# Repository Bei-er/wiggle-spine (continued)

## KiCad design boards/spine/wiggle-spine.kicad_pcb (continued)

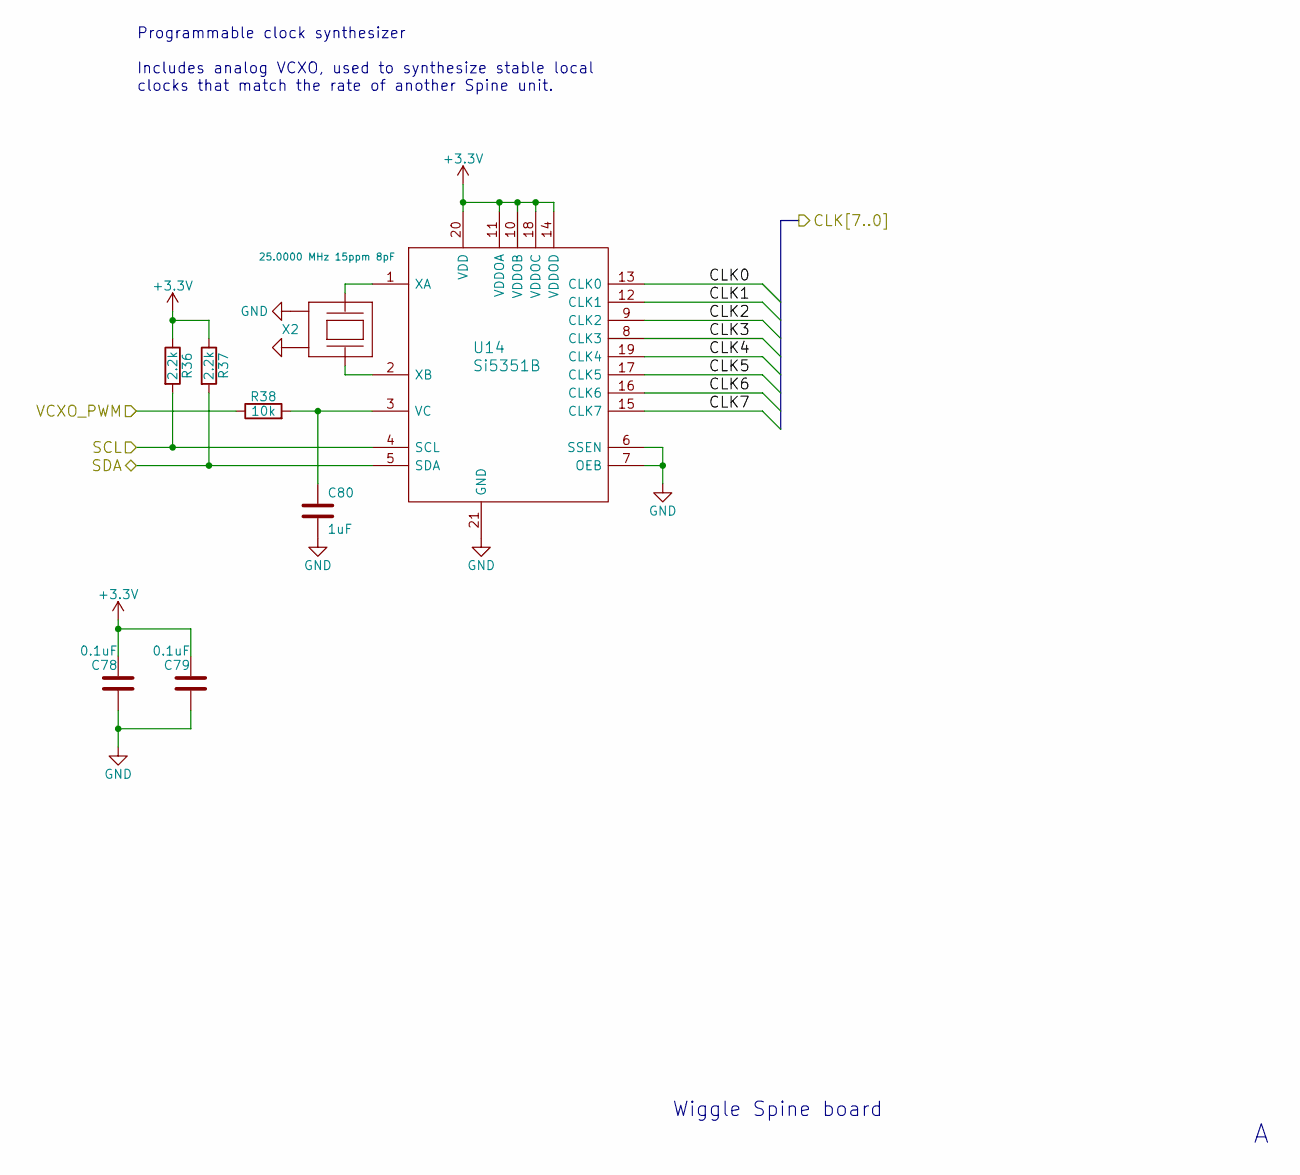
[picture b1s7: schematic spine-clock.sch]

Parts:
C78, C79: 0.1uF; C_0805
C80: 1uF; C_0805
R36, R37: 2.2k; R_0805
R38: 10k; R_0805
U14: Si5351B; QFN-20-1EP_4x4mm_Pitch0.5mm
X2: 25.0000 MHz 15ppm 8pF; crystal_FA238-TSX3225

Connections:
/Clock Source/CLK0: U14.13 (CLK0); also elsewhere on the board
/Clock Source/CLK1: U14.12 (CLK1); also elsewhere on the board
/Clock Source/CLK2: U14.9 (CLK2); also elsewhere on the board
/Clock Source/CLK3: U14.8 (CLK3); also elsewhere on the board
/Clock Source/CLK4: U14.19 (CLK4); also elsewhere on the board
/Clock Source/CLK5: U14.17 (CLK5); also elsewhere on the board
/Clock Source/CLK6: U14.16 (CLK6); also elsewhere on the board
/Clock Source/CLK7: U14.15 (CLK7); also elsewhere on the board
/Clock Source/VCXO_PWM: R38.1; also elsewhere on the board
/FPGA/CLK_SCL: R36.2, U14.4 (SCL); also elsewhere on the board
/FPGA/CLK_SDA: R37.2, U14.5 (SDA); also elsewhere on the board
GND: C78.1, C79.1, C80.2, U14.6 (SSEN), U14.7 (OEB), U14.21 (GND), X2.2, X2.4; also elsewhere on the board
unnamed: C80.1, R38.2, U14.3 (VC)
unnamed: U14.1 (XA), X2.1
unnamed: U14.2 (XB), X2.3

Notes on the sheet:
Programmable clock synthesizer Includes analog VCXO, used to synthesize stable local clocks that match the rate of another Spine unit.
Wiggle Spine board

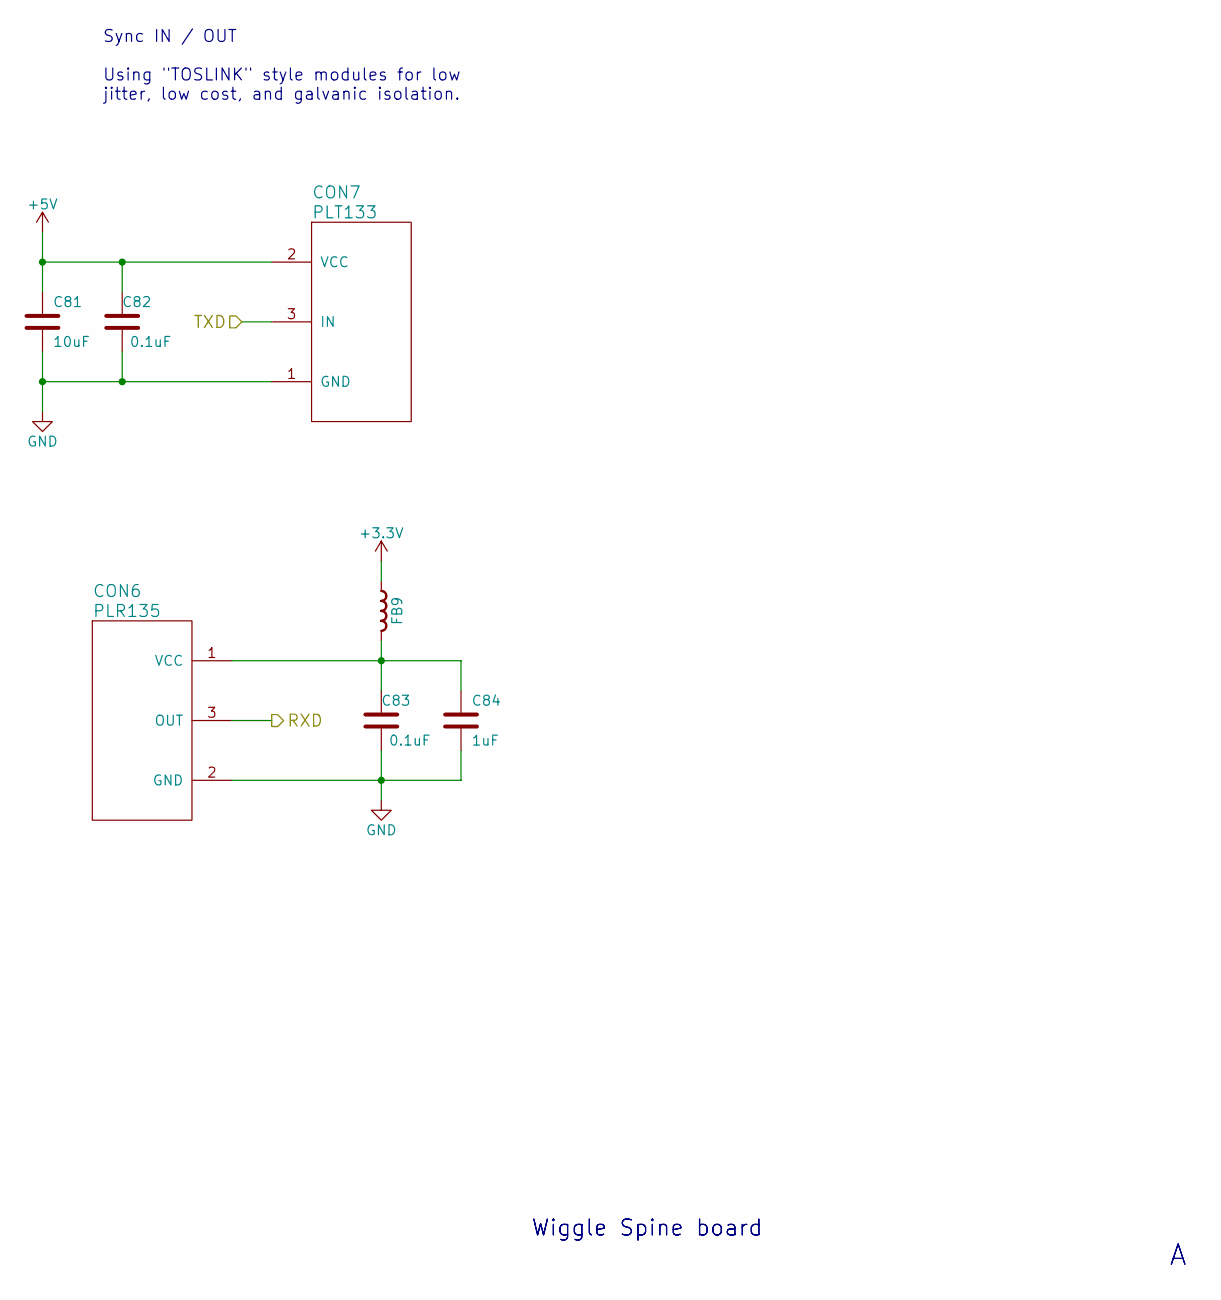
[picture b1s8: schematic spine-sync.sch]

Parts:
C81: 10uF; C_1206
C82, C83: 0.1uF; C_0805
C84: 1uF; C_0805
CON6: PLR135; Everlight-PLR135-T8
CON7: PLT133; Everlight-PLT133-T6A
FB9: Ferrite bead; R_0805

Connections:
+5V: C81.1, C82.2, CON7.2 (VCC); also elsewhere on the board
/FPGA/SYNC_TXD: CON7.3 (IN); also elsewhere on the board
/Sync In/Out/RXD: CON6.3 (OUT); also elsewhere on the board
GND: C81.2, C82.1, C83.1, C84.2, CON6.2 (GND), CON7.1 (GND); also elsewhere on the board
unnamed: C83.2, C84.1, CON6.1 (VCC), FB9.2

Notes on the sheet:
Sync IN / OUT Using "TOSLINK" style modules for low jitter, low cost, and galvanic isolation.
Wiggle Spine board

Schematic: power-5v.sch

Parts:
C43, C44, C50, C51: 22uF; c_elec_6.3x7.7
C45, C46, C52: 10uF; C_1206
C47: 1uF; C_0805
C48: 0.1uF; C_0805
C49: 100pF; C_0805
D6: BAT54 2x common cathode; SOT-23
L1: 22uH; Neosid_Inductor_SM-NE127
R23, R27: 100k; R_0805
R24: 150; R_0805
R25: 27k 1%; R_0805
R26: 5.1k 1%; R_0805
U7: RT8299A; SOIC-8-1EP_3.9x4.9mm_Pitch1.27mm

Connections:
+24V: C43.1, C44.1, C45.1, C46.1, R23.1, U7.2 (VIN); also elsewhere on the board
/Power/5-24V to 5V Converter/CONVERTED_5V_OKAY: R27.1, U7.7 (PGOOD); also elsewhere on the board
/Power/USB Power Output/5V_IN: C50.1, C51.1, C52.1, D6.1 (A), D6.2 (A), L1.2, R25.2, R27.2; also elsewhere on the board
GND: C43.2, C44.2, C45.2, C46.2, C47.2, C49.1, C50.2, C51.2, C52.2, R26.1, U7.4 (GND), U7.9 (GND); also elsewhere on the board
unnamed: C47.1, U7.8 (VCC)
unnamed: C48.1, L1.1, R24.2, U7.3 (SW)
unnamed: C48.2, D6.3 (K), U7.1 (BOOT)
unnamed: C49.2, R24.1
unnamed: R23.2, U7.6 (EN)
unnamed: R25.1, R26.2, U7.5 (FB)

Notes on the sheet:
Open drain output
Bootstrap assistance for Vin < 5.5
Wiggle Spine board
High efficiency DC-DC converter, 5V at 3A from 5-24V DC. This 5V rail is shared by the USB output (up to 2A), the modules (100mA each), and all FPGA and USB controller power rails.

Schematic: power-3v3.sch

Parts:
C53, C59, C60: 22uF; c_elec_6.3x7.7
C54, C55, C61: 10uF; C_1206
C56: 1uF; C_0805
C57: 0.1uF; C_0805
C58: 100pF; C_0805
D7: BAT54 2x common cathode; SOT-23
L2: 22uH; Neosid_Inductor_SM-NE127
R28: 150; R_0805
R29: 16k 1%; R_0805
R30: 5.1k 1%; R_0805
U8: RT8299A; SOIC-8-1EP_3.9x4.9mm_Pitch1.27mm

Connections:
+5V: C53.1, C54.1, C55.1, D7.1 (A), D7.2 (A), U8.2 (VIN), U8.6 (EN); also elsewhere on the board
GND: C53.2, C54.2, C55.2, C56.2, C58.1, C59.2, C60.2, C61.2, R30.1, U8.4 (GND), U8.9 (GND); also elsewhere on the board
unnamed: C56.1, U8.8 (VCC)
unnamed: C57.1, L2.1, R28.2, U8.3 (SW)
unnamed: C57.2, D7.3 (K), U8.1 (BOOT)
unnamed: C58.2, R28.1
unnamed: R29.1, R30.2, U8.5 (FB)

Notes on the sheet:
Bootstrap assistance diode; see RT8299A data sheet
Wiggle Spine board
High efficiency DC-DC converter, 3.3V at 3A

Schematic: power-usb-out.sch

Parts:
C62: 1uF; C_0805
C63, C64: 0.1uF; C_0805
CON3: USB-A; USB_A_Vertical
F2: 2A PTC; R_1812
FB5, FB6: Ferrite bead; R_0805
R31, R32: 100k; R_0805
U9: SiP32408; TDFN4

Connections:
/FPGA/VBUS_DOWNSTREAM_EN: R31.1, U9.3 (EN); also elsewhere on the board
/Power/USB Power Output/5V_IN: C62.1, R31.2, U9.1 (IN); also elsewhere on the board
Earth: CON3.5 (shield); also elsewhere on the board
GND: C62.2, C63.1, C64.1, FB6.1, R32.2, U9.2 (GND), U9.5 (GND); also elsewhere on the board
unnamed: C63.2, F2.1, R32.1, U9.4 (OUT)
unnamed: C64.2, F2.2, FB5.1
unnamed: CON3.1 (VCC), FB5.2
unnamed: CON3.2 (D-), CON3.3 (D+)
unnamed: CON3.4 (GND), FB6.2

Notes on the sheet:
Not the main +5V rail; this is intended to draw power from the DC-DC converter only, not the USB-B input.
USB power output, 5V 2A. Intended to power a small computer, like the Raspberry Pi 2. Optional hardware watchdog timer, implemented in the FPGA.
Wiggle Spine board

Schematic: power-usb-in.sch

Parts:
C65, C68, C69: 0.1uF; C_0805
C66, C67: 1uF; C_0805
C70, C71: 10uF; C_1206
D8: 8.5VWM; SOT-23
Q2: 2N7002P; SOT-23
R33: 100k; R_0805
R34: 2.2k; R_0805
U10, U11: SiP32408; TDFN4

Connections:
+5V: C68.2, C69.2, C70.1, C71.1, D8.1 (K), D8.2 (K), U10.4 (OUT), U11.4 (OUT); also elsewhere on the board
/Power/5-24V to 5V Converter/CONVERTED_5V_OKAY: Q2.1 (G), U11.3 (EN); also elsewhere on the board
/Power/USB Power Output/5V_IN: C67.1, U11.1 (IN); also elsewhere on the board
/Power/VBUS_UPSTREAM: C66.1, R33.1, U10.1 (IN); also elsewhere on the board
GND: C65.1, C66.2, C67.2, C68.1, C69.1, C70.2, C71.2, D8.3 (A), Q2.2 (S), U10.2 (GND), U10.5 (GND), U11.2 (GND), U11.5 (GND); also elsewhere on the board
unnamed: C65.2, R33.2, R34.1, U10.3 (EN)
unnamed: Q2.3 (D), R34.2

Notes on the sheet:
When USB power is available, route it to the +5V rail (with reverse current protection) When/if external 5V becomes available, switch to it softly, then draw no power from upstream USB.
(High-Z logic input)
Wiggle Spine board
Transient clamping

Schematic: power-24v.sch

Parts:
C72: 0.1uF; C_0805
C73: 1uF; C_0805
CON4: 2.5mm 5-24V 5A; BARREL_JACK
CON5: 5-24V 16A; TerminalBlock_Pheonix_PT-3.5mm_4pol
D9: 8.5VWM; SOT-23
FB7, FB8: Ferrite bead; R_0805
Q3: AOD4189; TO-252-2Lead
R35: 100k; R_0805

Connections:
+24V: C73.1, D9.1 (K), D9.2 (K), Q3.3 (S); also elsewhere on the board
/Power/5-24V Power Input/POWER_IN: C72.2, CON4.1, CON5.1, CON5.2, Q3.2 (D)
Earth: FB7.2; also elsewhere on the board
GND: FB8.2; also elsewhere on the board
GNDPWR: C72.1, C73.2, CON4.2, CON4.3, CON5.3, CON5.4, FB7.1, FB8.1, R35.2; also elsewhere on the board
unnamed: D9.3 (A), Q3.1 (G), R35.1

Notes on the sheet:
Reverse polarity protection
Power input options
High power return, from modules
Wiggle Spine board
Main (digital) ground net
Shield ground

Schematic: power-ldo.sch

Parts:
C74, C76: 0.1uF; C_0805
C75, C77: 1uF; C_0805
U12: TCR2EF25; SOT-23-5
U13: TCR2EF12; SOT-23-5

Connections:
+1V2: C77.1, U13.5 (Vout); also elsewhere on the board
+2V5: C75.1, C76.2, U12.5 (Vout), U13.1 (Vin), U13.3 (CONTROL); also elsewhere on the board
GND: C74.1, C75.2, C76.1, C77.2, U12.2 (GND), U13.2 (GND); also elsewhere on the board

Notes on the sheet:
Low voltage / low current LDO regulators for FPGA
1.2v = FPGA core voltage
2.5v = FPGA NVCM programming voltage (Some circuits approximate this with a diode drop from 3.3v, but that's pretty dirty and these LDOs are about as cheap as a diode.)
Wiggle Spine board

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
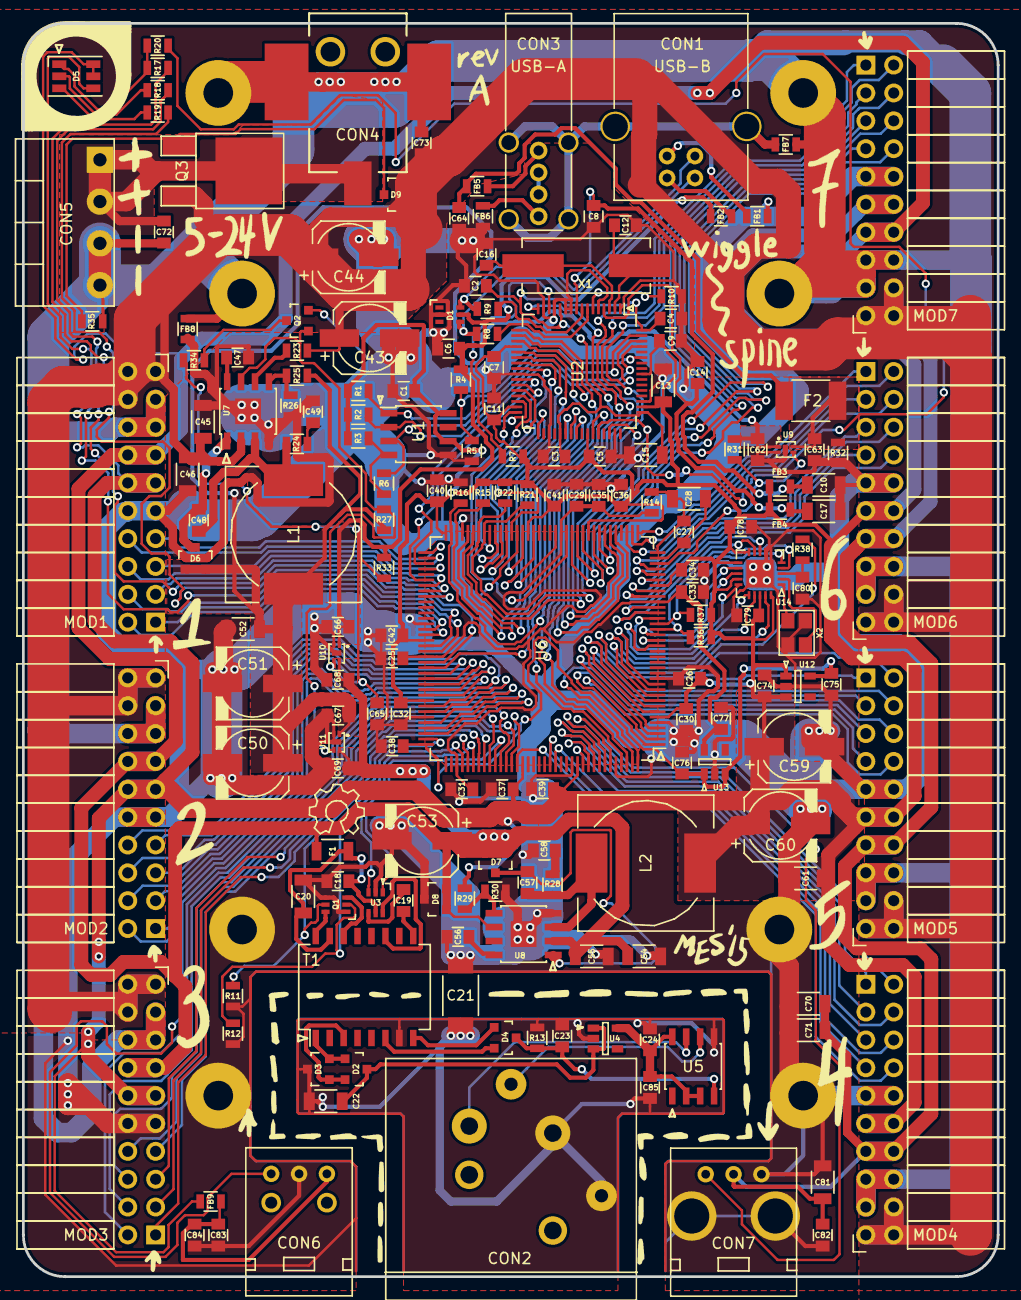
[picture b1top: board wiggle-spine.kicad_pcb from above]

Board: 2 copper layers, 88.9 x 114.3 mm, 179 parts (0 on the bottom side), 172 nets.

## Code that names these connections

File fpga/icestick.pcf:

# Temporary pin constraints for a modified icestick board

set_io CLK12 21

set_io RS232_TX 8
set_io RS232_RX 9

set_io DMX_TX1 87
set_io DMX_TX2 88
set_io DMX_GATE1 90
set_io DMX_GATE2 78   # Zapped pin 91 on my prototype...

set_io RED_N 79
set_io GREEN_N 80
set_io BLUE_N 81

set_io LED5 95
set_io LED4 96
set_io LED3 97
set_io LED2 98
set_io LED1 99

set_io DEBUG[0] 112
set_io DEBUG[1] 113
set_io DEBUG[2] 114
set_io DEBUG[3] 115
set_io DEBUG[4] 116
set_io DEBUG[5] 117
set_io DEBUG[6] 118
set_io DEBUG[7] 119

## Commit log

2015-10-26 Draft idea for the wordmark
2015-10-26 Clean up spacing and paths
2015-10-26 Convert to SVG
2015-10-26 Path cleanup on leading tail of sine wave
2015-10-26 Rasterized logo
2015-10-27 Update README.md
    The 14 limit isn't total, it's per spine board
2015-10-27 Update README.md
    Tidy... smaller image, try out some capitals and see how it feels.
2015-10-27 wider!
2015-10-28 Collect some data sheets of candidate PSUs
    Thanks to @chippolev for the Bicker recommendation!
2015-11-07 Logic libraries used for our LTspice sim
2015-11-07 Sim model for an experimental DMX isolator
2015-11-07 Another point
2015-11-08 Untested draft of the DMX isolator subcircuit
2015-11-08 Tidy
2015-11-08 Get the BOM started
2015-11-08 Fuss with the USB
2015-11-09 USB port: ESD, crystal, eeprom
2015-11-09 More schematic work: module ports and USB
2015-11-09 Getting the FPGA set up
2015-11-10 Pick better capacitors :)
2015-11-11 Ignore generated BOM files
2015-11-17 Early power management work
2015-11-18 Split up the power schematic
2015-11-18 Power source switching
2015-11-18 Power management and such
2015-11-19 Clock generator, sync connectors, title blocks
2015-11-19 Library updates
2015-11-19 Start keeping BOM and schematic plots in git?
2015-11-19 Adding prototype materials for reference
2015-11-24 Work-in-progress graphic README
2015-11-24 Rasterized work-in-progress intro, for reference
2015-11-25 Patterns in space and time~
2015-11-29 Ignore Mac OS detritus
2015-11-29 Fixes for shield grounds and module numbering
2015-11-29 Schematic footprint and refdes work
2015-11-30 What a mess
2015-11-30 Real footprint for DMX
2015-11-30 More footprints done
2015-11-30 Some more component placement
2015-11-30 Add Gitter badge
2015-11-30 Rough component placement
2015-11-30 More footprint fixes, and pin-1 dots
2015-11-30 Page things
2015-12-01 Component clustering around top and bottom I/O ports
2015-12-01 Try 2.7" width
    Probably too narrow to fit the DCDCs, but it looks nice doesn't it.
2015-12-01 More component packing
    If this routing is at all realistic, maybe 2.7" works after all. Haven't placed the DCDCs yet, but I think they'll fit.
2015-12-01 Fix MOD pinouts, and layout for 2.7x5.2in
2015-12-01 Adjust holes, pmod spacing, rounded corners
2015-12-01 Ordered LEDs to test
2015-12-01 Simpler indicator LED strategy
2015-12-01 Save room for a Wiggleport logo
2015-12-01 Nudge
2015-12-02 Fix some 6-pin packages
    I had several of these mislabeled as SOT23-6, but there are no SOT23-6 parts here. The LDOs are SOT23-5, and the others (TVS diode array and inverters) are in the smaller SC-88 package.
2015-12-02 Footprint updates
2015-12-02 Separated ground planes, starting on design rules
2015-12-02 Some 24V power routing
2015-12-03 24V power routing
2015-12-03 Switch to a ferrite bead with 6A current rating
2015-12-04 Bulk adjust for 9mil trace / 10mil space
    This is a compromise between the QFP packages and the Othermill with a 10 mil endmill :)
2015-12-04 Some routing, especially on the isolated DMX side
2015-12-05 Adopt the Contributor Covenant 1.3.0
2015-12-05 More routing, and QFN footprint tweaks
2015-12-06 More work on the intro graphic
2015-12-06 Order and routing for FIFO parallel bus
2015-12-06 Clock routing
2015-12-06 Starting module routing
2015-12-06 More swapping and rerouting on the FPGA
2015-12-07 Routing: GPIOs, mid-current power busses
2015-12-07 Two layers should be enough
2015-12-07 Fighting with kicad, not sure if the keepouts are working
2015-12-07 DRC pass, 9 unrouted
2015-12-07 Fully routed, DRC pass
2015-12-07 Tweaking power and ground planes
2015-12-07 Yikes, fix GNDPWR/GND overlap
    Not sure why the last DRC missed this. Zones still fighting with each other when they overlap?
2015-12-07 No NPTH holes
2015-12-07 Fix Edge.Cuts layer
2015-12-07 Landscape orientation
    Trying to work around a possible otherplan issue
2015-12-07 Early draft gerbers
2015-12-07 Move Sync TX trace further from DMX port
2015-12-07 More tweaks for nicer ground plane layout
2015-12-15 Updated to latest schematic
2015-12-15 Boilerplate FT2232H config with our assigned USB IDs
2015-12-15 Boilerplate for the FPGA
    Just getting the build system and such working so we can blink a LED.
2015-12-16 Generating test signals for bringing up the DMX isolator
2015-12-16 DMX isolator "U" test
2015-12-16 Refactoring
2015-12-16 Generate some DMXish test signals
2015-12-16 Green and purple "hello world" for the DMX port
2015-12-17 Test 512 slots of DMX
    Having some issues when removing DEBUG. Not sure if it's my fault or the synthesizer atm.
2015-12-19 For FPGA testing, start using the iceprog SRAM hack
2015-12-19 First round of DMX isolator simplifications
    - Removed RC filters on gate drive; they aren't accurate enough to prevent the FPGA from destroying the FETs with bad drive frequencies or duty cycles. I'm planning on spec'ing a polyfuse to protect 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
    - Removed fancypants schmitt trigger nonsense in the demodulator. This was just oscillating and wasn't working like it did in simulation at all, but it turns out we can just use the '485 driver input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
2015-12-20 Redraw DMX isolator based on latest simplifications
2015-12-20 More simplification and BOM optimization
    Thanks for the hints on the ST485 and dual-FETs, @mikelectricstuf!
2015-12-21 BOM tweaks, starting DC/DC fixes
    VCC is not active until EN goes high, so EN must be
    connected to VIN via the 100k resistor. Internal resistance
    is 5k to a 3V zener.
2015-12-22 BOM cleanup
    Especially fix the confusing and mostly incorrect Mfg/Mfr stuff that I inherited from somewhere.
2015-12-22 Capacitor upgrades, BOM tidying
2015-12-22 About 50% dimmer blue LED when FPGA is unconfigured
    This seems a good compromise between visibility while debugging and unobtrusiveness during normal operation.
2015-12-23 Schematics stabilizing for next proto, starting PCB updates
2015-12-23 Draft for new mechanical layout
2015-12-23 Found room for the sync plugs and LED
2015-12-23 Y2 capacitors are a thing!
2015-12-23 4mm gap and DMX secondary placement
2015-12-23 Nicer 1808 capacitor footprint with 4mm gap
2015-12-23 Placement draft with everything other than SMPS on board
2015-12-23 Off-board SMPS placement
    Much happier with the high current paths this time
2015-12-23 Making room for the 24-to-5 regulator
2015-12-23 Flip DMX TX to improve 5V locality
2015-12-23 Trying a dashed silkscreen outline for the isolation barrier
2015-12-24 Ripup copper, good placement for DMX secondary
2015-12-24 Another pass at placement completed
2015-12-24 Happy little fills
2015-12-24 Hand edit to duplicate gap boundaries on bottom layer
2015-12-24 Via stitching and net fixes for DMXGND
2015-12-24 More zone placement.. concerned about +24
2015-12-24 Progress on zone and 3v3 filter layout
2015-12-25 Working on module power routing
2015-12-25 More power routing, mounting hole tweak, DRC
2015-12-25 DRC tweak, 0.2mm clearance
    This is the largest we can get away with, due to the TDFN4 footprint. It's a litlte over 7 mils, which is over oshpark's 6 mil minimum.
2015-12-25 DMX secondary routed
2015-12-25 GND distribution, DMX via tweaks
2015-12-25 Feeling better about GNDPWR and GND along the edges
2015-12-25 Wiggle through the thick verticals
2015-12-25 Lots more thick power routing
2015-12-25 More power routing, making room for the 5V vertical
2015-12-26 Happy with the +5 vertical for now
2015-12-26 Redo component annotation
    Noticed the module numbers were wrong after the last reannotation, so this seemed like a good time to reannotate again.
2015-12-26 Route some port GPIOs
    but let's not get too carried away before placing everything...
2015-12-26 Making room for USB port components
2015-12-27 5V_IN to 5V switch
2015-12-27 More power and signal routing, 5V switches mostly placed
2015-12-27 More work on the loops around the 24V dcdc
2015-12-27 Tidying up before another placement round
2015-12-27 Making room for U9 and F2
2015-12-27 Placed 5V downstream switch and fuse
2015-12-27 More placement around U2. So close.
2015-12-27 Fully placed again, for now
2015-12-27 Ripup chip undersides, getting signals into vias
2015-12-28 More dense routing in the bottom-right
2015-12-28 More GPIO routing. Almost forgot the EEPROM
2015-12-28 Squeeze the via forest
2015-12-28 Think everything fits under U2 that needs to
2015-12-28 Preparing to route RGB LED along top
2015-12-29 Think we have all the GPIOs collected`
2015-12-29 Ground star retied, preparing for repinning FPGA
2015-12-29 Ripup movable FPGA traces, route the few immovable ones
2015-12-29 DRC, yeah
2015-12-29 Constructing FPGA pinout, DRC
2015-12-29 More FPGA routing, DRC
2015-12-29 FPGA I/Os routed
2015-12-29 Sneaky 2.5v trace
2015-12-29 Working on Vcore routing
2015-12-29 Tricky 1.2v route
2015-12-29 Most of the Vcore routed
2015-12-29 Vcore, DRC
2015-12-29 More power routing, DRC
2015-12-30 10 left
2015-12-30 6 left, DRC
2015-12-30 Almost there
2015-12-30 Seems to be fully routed
2015-12-30 Fully routed, passes DRC. Zone cleanup.
2015-12-30 Tidying, DRC, 0 unconnected
2015-12-30 Candidate gerbers for Rev A
2015-12-30 Starting front silk tidy
2015-12-30 Capacitor silkscreen fix
2015-12-30 More capacitor silk tweaks
2015-12-30 Silk-in-pad fixes spotted by @oresk
2015-12-30 Gerber format and silkscreen fixes
2015-12-30 Zone cleanup, track obsession, DRC
2015-12-31 Such zone fussing
2015-12-31 Enough zone fussing?
2015-12-31 Such zone, very fussed
2015-12-31 Gerber update prior to silkscreen art
2015-12-31 Dimension tidy
2015-12-31 Rotate board
    This seems to be the easiest way to keep the text orientation as I'd like it, and the board fits this way now
2015-12-31 Remove heavy dashed border, to be replaced with a sketched version
2015-12-31 Hand drawn front silkscreen
2015-12-31 Subtle OSHW logo
2015-12-31 Back silkscreen design
2015-12-31 Fix overlap with "DMX OUT" label
2015-12-31 Fix stray reference on front silk from OSHW logo
2015-12-31 Plot solder paste layer
2015-12-31 Ordered new parts added in Wiggle Spine A
2016-01-01 Switch from .ice.txt to .asc extension
    https://twitter.com/oe1cxw/status/682967525102059522
2016-01-11 Replace TVS diode D1
    Previous part from NXP is going end-of-life, new part should be a drop-in replacement from Diodes Inc.
2016-01-12 Starting to document the wigglemod port
2016-01-12 Alternate version of the logo
2016-01-13 Updated colors and labels
2016-01-14 Work in progress module definition
2016-01-14 FPGA
2016-01-14 FPGA explanation
2016-01-29 Fussy tweaks
2016-02-01 Little square wigl logo
2016-02-01 Rearrange wiggle-spine repo structure
2016-02-01 Slight patch until the new site is up
2016-02-01 CERN license for the open hardware
2016-02-05 Migrate from Gitter to Freenode
2016-02-07 A few photos to document the board build
2016-02-07 Rescope the README to just Wiggle Spine, link to wiggleport.org
2016-02-07 Early link to the main site
2016-02-08 Heading tweak
2016-02-17 Update to latest contributor covenant
